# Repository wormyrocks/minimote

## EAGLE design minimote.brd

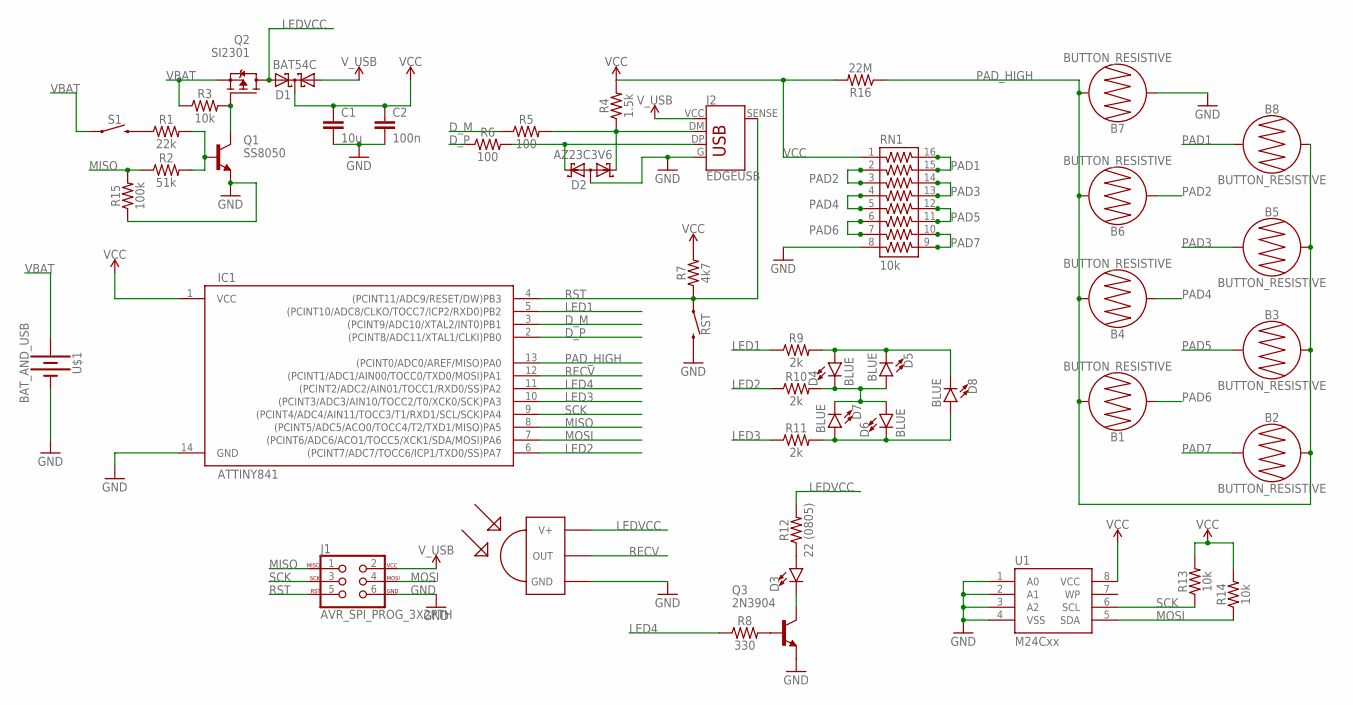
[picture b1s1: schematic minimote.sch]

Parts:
B1, B2, B3, B4, B5, B6, B7, B8: BUTTON_RESISTIVE; BUTTON-CONDUCTIVE
C1: 10u; 0603
C2: 100n; 0603
D1: BAT54C; SOT23
D2: AZ23C3V6; SOT23
D3: LED3MM; LED_3MM
D4, D5, D6, D7, D8: BLUE; LED-0603
IC1: ATTINY841; SOIC14N
J1: AVR_SPI_PROG_3X2PTH; 2X3
J2: EDGEUSB; USBPCB
Q1: SS8050; SOT23
Q2: SI2301; SOT23
Q3: 2N3904; SOT23-BEC
R1: 22k; 0603
R2: 51k; 0603
R3, R13, R14: 10k; 0603
R4: 1.5k; 0603
R5, R6: 100; 0603
R7: 4k7; 0603
R8: 330; 0603
R9, R10, R11: 2k; 0603
R12: 22 (0805); 0805
R15: 100k; 0603
R16: 22M; 0603
RN1: 10k; 742-16NS
RST: MOMENTARY-SWITCH-SPST-SMD-5.2-REDUNDANT; TACTILE_SWITCH_SMD_5.2MM
S1: MOMENTARY-SWITCH-SPST-SMD-5.2-REDUNDANT; TACTILE_SWITCH_SMD_5.2MM
U1: M24Cxx; SO08-EIAJ
U$1: BAT_AND_USB; PUNCHOUT_USB
U$2: TSOP1837; TSOP18XX

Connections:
D_M: IC1.3 ((PCINT9/ADC10/XTAL2/INT0)PB1), R5.1
D_P: IC1.2 ((PCINT8/ADC11/XTAL1/CLKI)PB0), R6.1
GND: B7.1, C1.2, C2.2, D2.3 (AA), IC1.14 (GND), J1.6, J2.G (GND), Q1.2 (E), Q3.E, R15.1, RN1.8, RST.3 (2), RST.4 (2), U1.1 (A0), U1.2 (A1), U1.3 (A2), U1.4 (VSS), U$1.B- (-), U$2.GND
LED1: IC1.5 ((PCINT10/ADC8/CLKO/TOCC7/ICP2/RXD0)PB2), R9.1
LED2: IC1.6 ((PCINT7/ADC7/TOCC6/ICP1/TXD0/SS)PA7), R10.1
LED3: IC1.10 ((PCINT3/ADC3/AIN10/TOCC2/T0/XCK0/SCK)PA3), R11.1
LED4: IC1.11 ((PCINT2/ADC2/AIN01/TOCC1/RXD0/SS)PA2), R8.1
LEDVCC: D1.2 (A2), Q2.3 (D), R12.2, U$2.VCC (V+)
MISO: IC1.8 ((PCINT5/ADC5/ACO0/TOCC4/T2/TXD1/MISO)PA5), J1.1, R2.1, R15.2
MOSI: IC1.7 ((PCINT6/ADC6/ACO1/TOCC5/XCK1/SDA/MOSI)P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), J1.4, R14.1, U1.5 (SDA)
unnamed: D3.A, R12.1
unnamed: D3.K (C), Q3.C
unnamed: Q3.B, R8.2
unnamed: Q1.3 (C), Q2.1 (G), R3.2
unnamed: Q1.1 (B), R1.2, R2.2
unnamed: R1.1, S1.3 (2), S1.4 (2)
unnamed: D2.1 (K2), J2.DP (D+), R6.2
unnamed: D2.2 (K1), J2.DM (D-), R4.1, R5.2
unnamed: D6.C, D7.A, D8.A, R11.2
unnamed: D4.C, D5.A, D6.A, D7.C, R10.2
unnamed: D4.A, D5.C, D8.C, R9.2
PAD1: B8.1, RN1.15, RN1.16
PAD2: B6.1, RN1.2, RN1.3
PAD3: B5.1, RN1.13, RN1.14
PAD4: B4.1, RN1.4, RN1.5
PAD5: B3.1, RN1.11, RN1.12
PAD6: B1.1, RN1.6, RN1.7
PAD7: B2.1, RN1.9, RN1.10
PAD_HIGH: B1.2, B2.2, B3.2, B4.2, B5.2, B6.2, B7.2, B8.2, IC1.13 ((PCINT0/ADC0/AREF/MISO)PA0), R16.1
RECV: IC1.12 ((PCINT1/ADC1/AIN00/TOCC0/TXD0/MOSI)PA1), U$2.OUT
RST: IC1.4 ((PCINT11/ADC9/RESET/DW)PB3), J1.5, J2.SENSE, R7.1, RST.1, RST.2 (1)
SCK: IC1.9 ((PCINT4/ADC4/AIN11/TOCC3/T1/RXD1/SCL/SC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), J1.3, R13.1, U1.6 (SCL)
VBAT: Q2.2 (S), R3.1, S1.1, S1.2 (1), U$1.B+ (+)
VCC: C1.1, C2.1, D1.3 (CC), IC1.1 (VCC), R4.2, R7.2, R13.2, R14.2, R16.2, RN1.1, U1.8 (VCC)
V_USB: D1.1 (A1), J1.2, J2.VCC (VBUS)

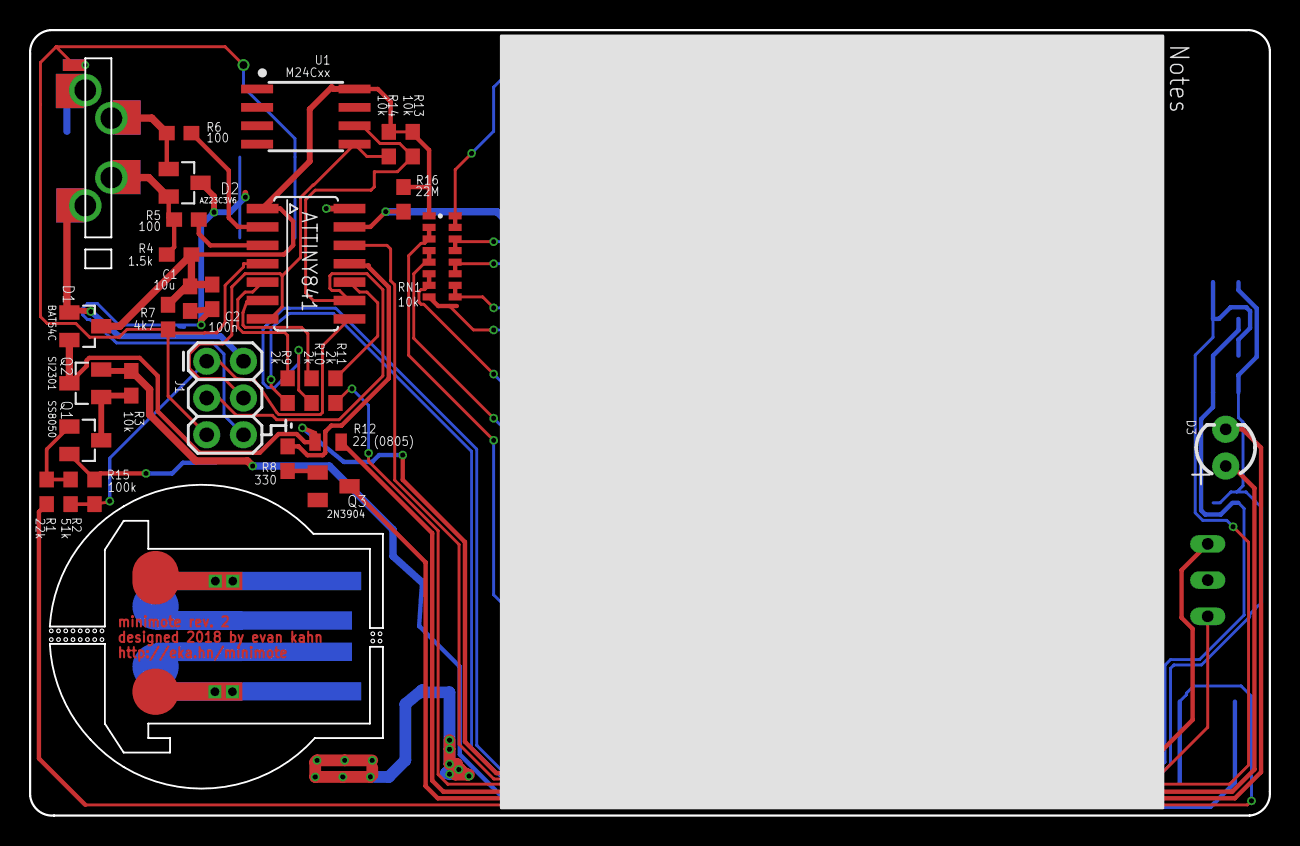
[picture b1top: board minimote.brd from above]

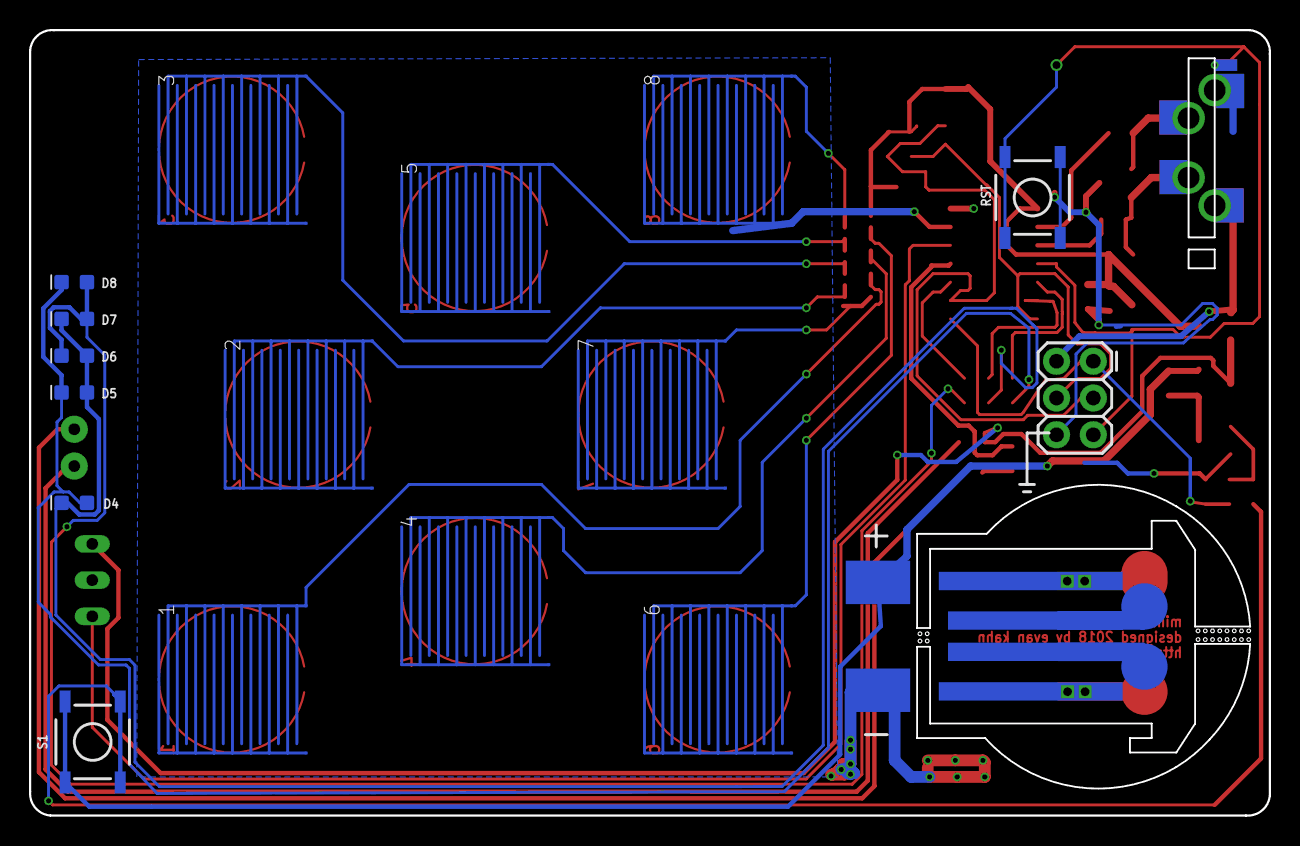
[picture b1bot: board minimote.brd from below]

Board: 2 copper layers, 85.6 x 54.2 mm, 46 parts (16 on the bottom side), 35 nets.

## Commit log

2018-03-05 moved parts around
2018-03-05 changed 3904 to smt component
2018-03-05 enlarged touch pads
2018-03-05 routed board
2018-03-05 cleaned up ground traces
2018-03-05 Cleaned up silkscreen
2018-03-05 cleaned up silkscreen layers
2018-03-05 Version submitted to DirtyPCBs
2018-03-06 fixed pwr ground short
2018-03-07 added footprint for i2c eeprom
2018-03-07 tidied up board layout
2018-03-28 updated resistor pack part
2018-04-01 Some board revisions and first firmware checkin
2018-04-01 major pcb revisions
2018-04-02 added library
2018-04-02 pause commit
2018-04-02 routed new board
2018-04-03 Rev 2 board sent to OSHPark

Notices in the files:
parts and their libraries:
SparkFun-LED: Licensing: Creative Commons ShareAlike 4.0 International - https://creativecommons.org/licenses/by-sa/4.0
resistor-array: Copyright (C) 2008, Bob Starr
